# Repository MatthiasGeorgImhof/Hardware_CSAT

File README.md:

# Hardware_CSAT

Hardware design files for 1x cubesat:
- [EPS board](https://github.com/MatthiasGeorgImhof/Hardware_CSAT/tree/master/eps_board)
  - batteries and battery management for solar cells charging
  - voltage regulatars
  - RTC clock
- [Avionics board](https://github.com/MatthiasGeorgImhof/Hardware_CSAT/tree/master/avionics_board)
  - IMU and magnetometer
  - sun detectors
  - magnetorquer control
- [Science board](https://github.com/MatthiasGeorgImhof/Hardware_CSAT/tree/master/sci_board_wo_switches)
  - cameras and imagers
- [Communication board](https://github.com/MatthiasGeorgImhof/Hardware_CSAT/tree/master/comm_board)
  - 915 MHz link
  - ethernet port for satelite modem

In addition, there is also
- [Auxilliary board](https://github.com/MatthiasGeorgImhof/Hardware_CSAT/tree/master/aux_board) that stands provides desktop power and connectivity
  - USB connection to computer
  - voltage regulators

Schematics & Layouts are done using KiCad V9.0

The corresponding software repos are [AUXL496_CSAT for the auxilliary board](https://github.com/MatthiasGeorgImhof/AUXL496_CSAT) and [SCIL496_CSAT for the science board](https://github.com/MatthiasGeorgImhof/SCIL496_CSAT). Software is based on a common architecture [Common_CSAT](https://github.com/MatthiasGeorgImhof/Common_CSAT).

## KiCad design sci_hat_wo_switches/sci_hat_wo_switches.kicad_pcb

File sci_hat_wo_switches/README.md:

# Science Board

- STM32L496VGTx
- 2x CAN buses
- 3x camera ports
- 1x I2C port

 "Science board")

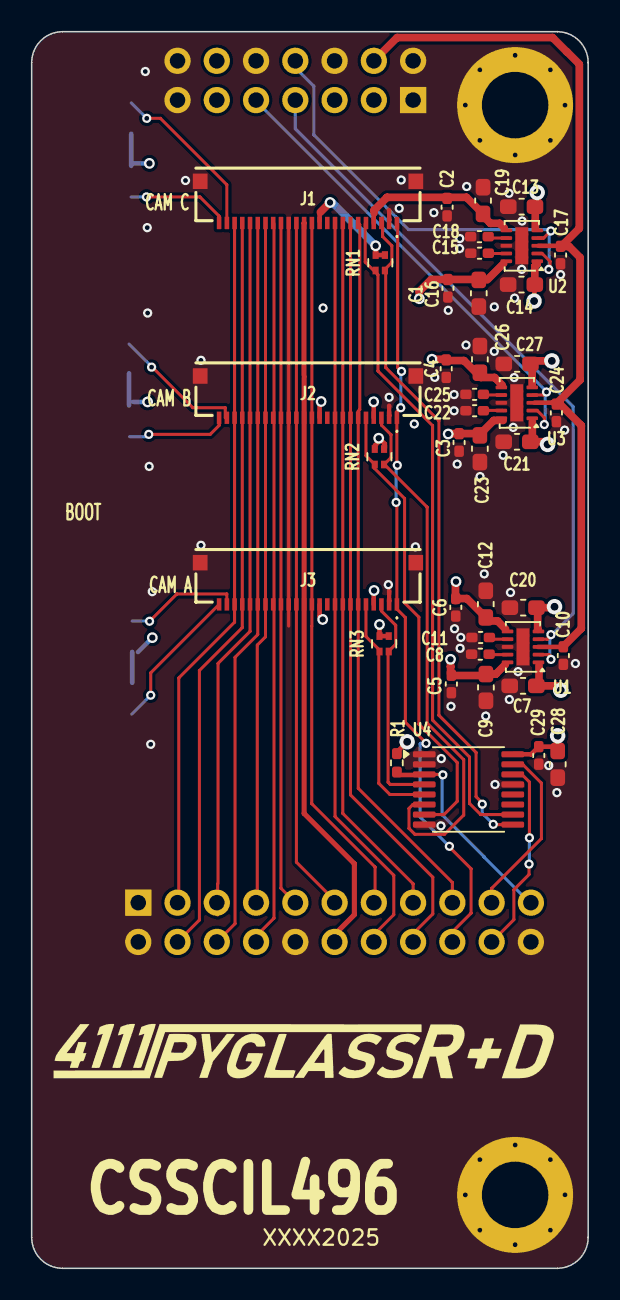
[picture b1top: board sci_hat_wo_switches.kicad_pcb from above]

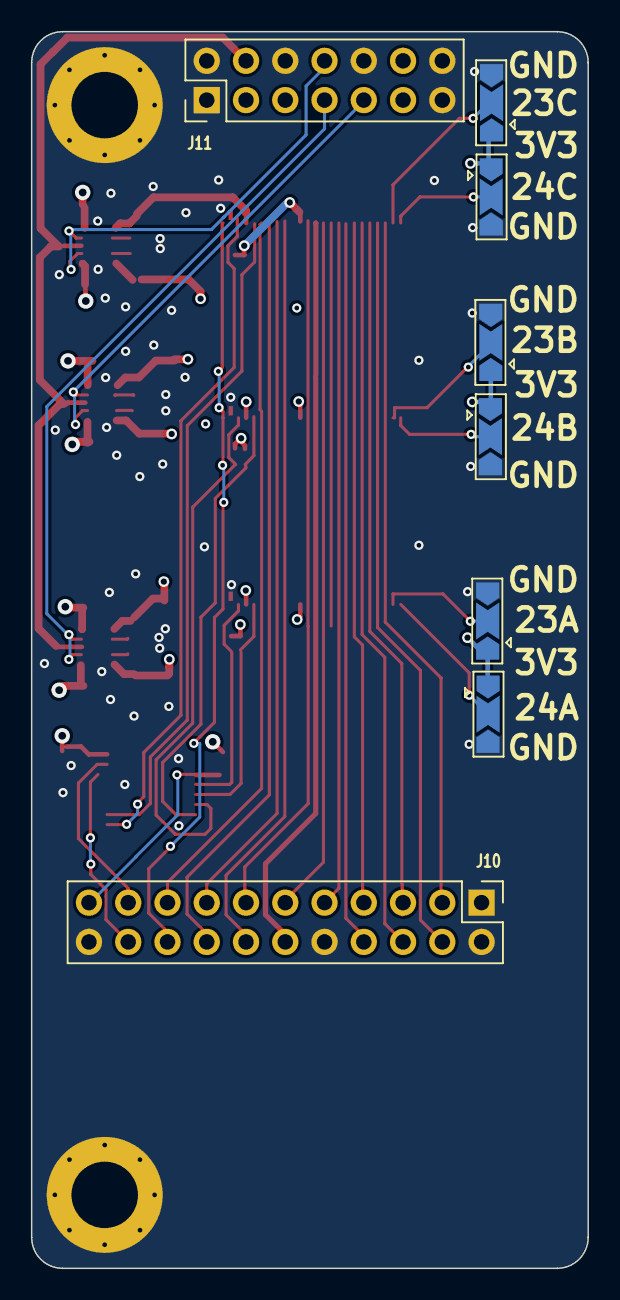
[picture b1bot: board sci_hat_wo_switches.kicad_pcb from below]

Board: 4 copper layers, 36.0 x 80.0 mm, 53 parts (8 on the bottom side), 52 nets.

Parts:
C1, C2, C3, C4, C5, C6, C10, C17, C24, C29: 100nF; C_0402_1005Metric_Pad0.74x0.62mm_HandSolder
C7, C13, C14, C20, C21, C27: 22uF; C_0603_1608Metric_Pad1.08x0.95mm_HandSolder
C8, C11, C15, C18, C22, C25: 220pF; C_0402_1005Metric_Pad0.74x0.62mm_HandSolder
C9, C12, C16, C19, C23, C26, C28: 10uF; C_0603_1608Metric_Pad1.08x0.95mm_HandSolder
H1, H2: MountingHole_Pad; MountingHole_4.3mm_M4_Pad_Via_Custom
J1, J2, J3: 10051922-2410EHLF; 100519222410EHLF
J10: Conn_02x11_Odd_Even; PinHeader_2x11_P2.54mm_Vertical
J11: Conn_02x07_Odd_Even; PinHeader_2x07_P2.54mm_Vertical
JP1, JP2, JP3, JP4, JP5, JP6: SolderJumper_3_Open; SolderJumper-3_P2.0mm_Open_TrianglePad1.0x1.5mm
NT1, NT2, NT3: NetTie_2; NetTie-2_SMD_Pad0.3mm
R1: 100K; R_0402_1005Metric_Pad0.72x0.64mm_HandSolder
RN1, RN2, RN3: 5K6; R_Array_Convex_2x0402_widepads
U1, U2, U3: TPS22968QDMGRQ1; WSON-10-1EP_2x3mm_P0.5mm_EP0.84x2.4mm
U4: TCA9546APWR; TSSOP-16_4.4x5mm_P0.65mm

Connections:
+1V8: C7.1, C14.1, C21.1, C28.1, C29.1, J11.5, R1.1, U1.1 (VIN1), U2.1 (VIN1), U3.1 (VIN1), U4.16 (VCC)
+2V8: C13.1, C20.1, C27.1, J11.3, U1.5 (VIN2), U2.5 (VIN2), U3.5 (VIN2)
+3.3V: C10.1, C17.1, C24.1, J11.4, U1.3 (VBIAS), U2.3 (VBIAS), U3.3 (VBIAS)
/CameraHat/1V8_A: C5.1, C9.1, J3.11, JP5.1 (A), JP6.1 (A), RN3.3 (R2.2), RN3.4 (R1.2), U1.10 (VOUT1)
/CameraHat/1V8_B: C3.1, C23.1, J2.11, JP3.1 (A), JP4.1 (A), RN2.3 (R2.2), RN2.4 (R1.2), U3.10 (VOUT1)
/CameraHat/1V8_C: C1.1, C16.1, J1.11, JP1.1 (A), JP2.1 (A), RN1.3 (R2.2), RN1.4 (R1.2), U2.10 (VOUT1)
/CameraHat/2V8_A: C6.1, C12.2, J3.4, U1.6 (VOUT2)
/CameraHat/2V8_B: C4.1, C26.2, J2.4, U3.6 (VOUT2)
/CameraHat/2V8_C: C2.1, C19.2, J1.4, U2.6 (VOUT2)
/CameraHat/Camera_A/A_GND: J3.2, NT3.1
/CameraHat/Camera_A/SCK: J3.5, RN3.1 (R1.1), U4.5 (SC0)
/CameraHat/Camera_A/SDA: J3.3, RN3.2 (R2.1), U4.4 (SD0)
/CameraHat/Camera_B/A_GND: J2.2, NT2.1
/CameraHat/Camera_B/SCK: J2.5, RN2.1 (R1.1), U4.7 (SC1)
/CameraHat/Camera_B/SDA: J2.3, RN2.2 (R2.1), U4.6 (SD1)
/CameraHat/Camera_C/A_GND: J1.2, NT1.1
/CameraHat/Camera_C/SCK: J1.5, RN1.1 (R1.1), U4.10 (SC2)
/CameraHat/Camera_C/SDA: J1.3, RN1.2 (R2.1), U4.9 (SD2)
/CameraHat/DCMI_00: J1.19, J2.19, J3.19, J10.6
/CameraHat/DCMI_01: J1.21, J2.21, J3.21, J10.4
/CameraHat/DCMI_02: J1.22, J2.22, J3.22, J10.3
/CameraHat/DCMI_03: J1.20, J2.20, J3.20, J10.5
/CameraHat/DCMI_04: J1.18, J2.18, J3.18, J10.7
/CameraHat/DCMI_05: J1.16, J2.16, J3.16, J10.9
/CameraHat/DCMI_06: J1.14, J2.14, J3.14, J10.11
/CameraHat/DCMI_07: J1.12, J2.12, J3.12, J10.13
/CameraHat/DCMI_HSYNC: J1.9, J2.9, J3.9, J10.14
/CameraHat/DCMI_PLXCLK: J1.17, J2.17, J3.17, J10.8
/CameraHat/DCMI_VSYNC: J1.7, J2.7, J3.7, J10.16
/CameraHat/ENABLE_A: J11.7, U1.2 (ON1), U1.4 (ON2)
/CameraHat/ENABLE_B: J11.9, U3.2 (ON1), U3.4 (ON2)
/CameraHat/ENABLE_C: J11.8, U2.2 (ON1), U2.4 (ON2)
/CameraHat/I2C_RST: J10.21, R1.2, U4.3 (RESET_N)
/CameraHat/I2C_SCK: J10.20, U4.14 (SCL)
/CameraHat/I2C_SDA: J10.19, U4.15 (SDA)
/CameraHat/PWRDN: J1.8, J2.8, J3.8, J10.15
/CameraHat/RESET: J1.6, J2.6, J3.6, J10.17
/CameraHat/STROBE: J1.1, J2.1, J3.1, J10.18
/CameraHat/XCLK: J1.13, J2.13, J3.13, J10.12
GND: C1.2, C2.2, C3.2, C4.2, C5.2, C6.2, C7.2, C8.2, C9.2, C10.2, C11.1, C12.1, C13.2, C14.2, C15.2, C16.2, C17.2, C18.1, C19.1, C20.2, C21.2, C22.2, C23.2, C24.2, C25.1, C26.1, C27.2, C28.2, C29.2, H1.1, H2.1, J1.15, J1.MP1, J1.MP2, J2.15, J2.MP1, J2.MP2, J3.15, J3.MP1, J3.MP2, J10.1, J10.2, J10.10, J10.22, J11.1, J11.2, J11.6, J11.10, J11.13, J11.14, JP1.3 (B), JP2.3 (B), JP3.3 (B), JP4.3 (B), JP5.3 (B), JP6.3 (B), NT1.2, NT2.2, NT3.2, U1.8 (GND), U1.11 (TPAD), U2.8 (GND), U2.11 (TPAD), U3.8 (GND), U3.11 (TPAD), U4.1 (A0), U4.2 (A1), U4.8 (GND), U4.13 (A2)
unnamed: J1.23, JP1.2 (C)
unnamed: J1.24, JP2.2 (C)
unnamed: J2.23, JP3.2 (C)
unnamed: J2.24, JP4.2 (C)
unnamed: J3.23, JP5.2 (C)
unnamed: J3.24, JP6.2 (C)
unnamed: C8.1, U1.9 (CT1)
unnamed: C11.2, U1.7 (CT2)
unnamed: C15.1, U2.9 (CT1)
unnamed: C18.2, U2.7 (CT2)
unnamed: C22.1, U3.9 (CT1)
unnamed: C25.2, U3.7 (CT2)

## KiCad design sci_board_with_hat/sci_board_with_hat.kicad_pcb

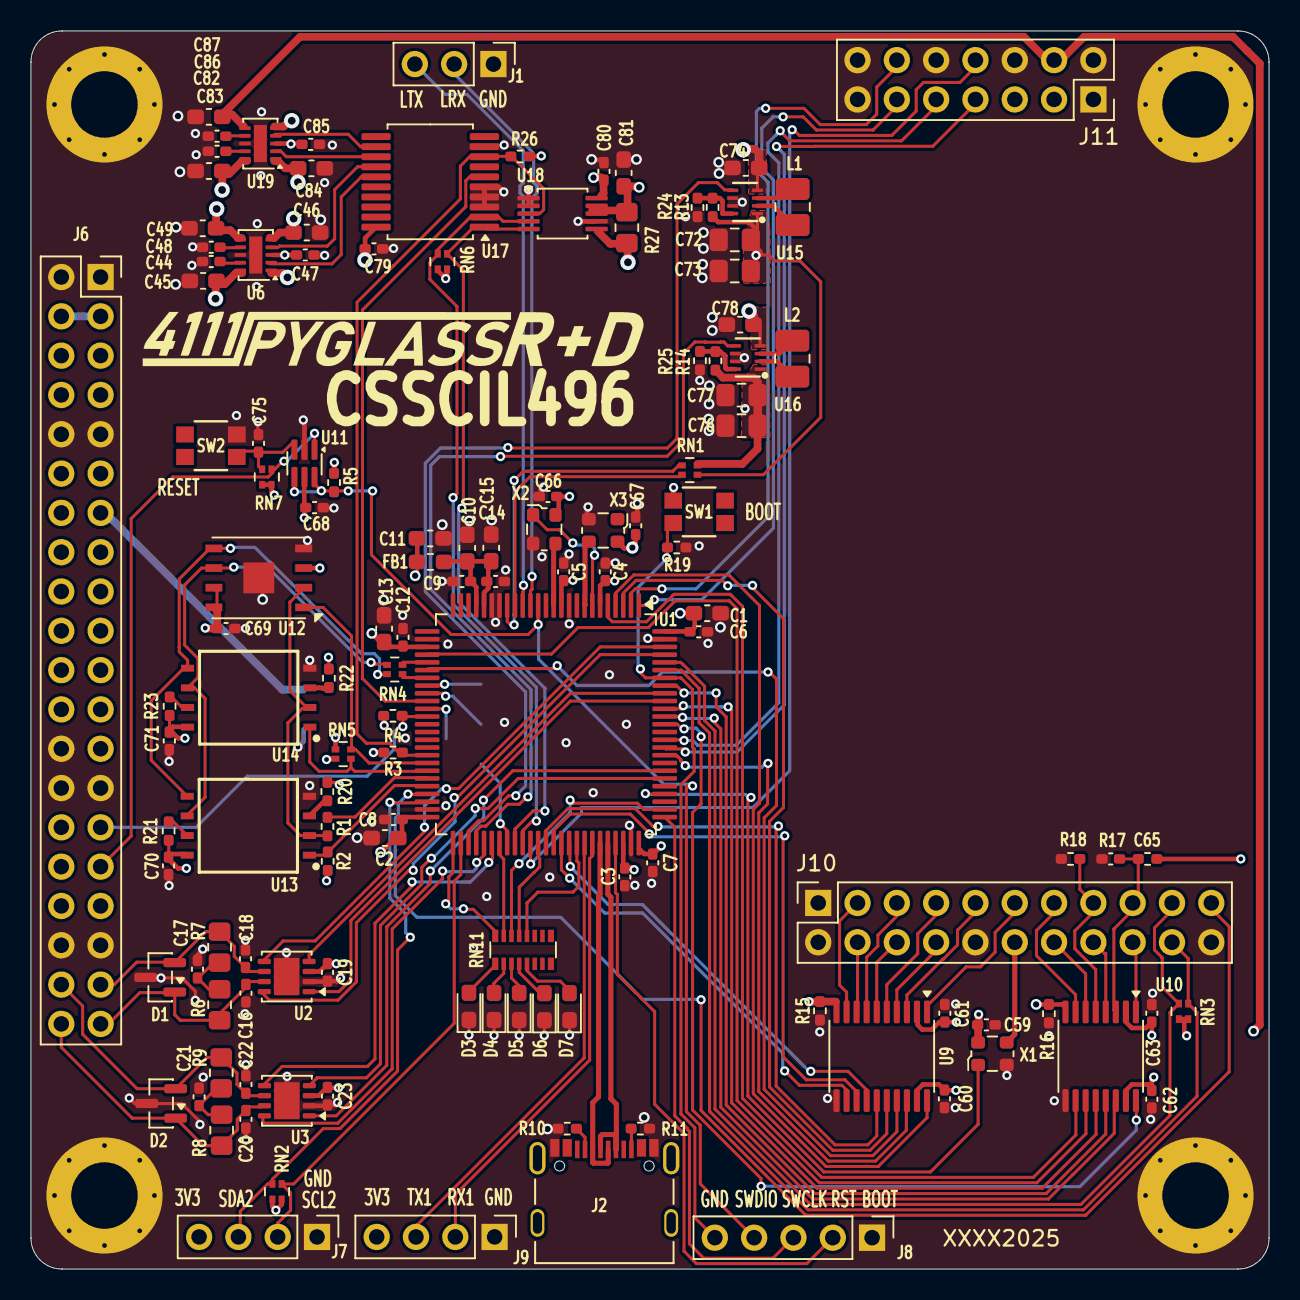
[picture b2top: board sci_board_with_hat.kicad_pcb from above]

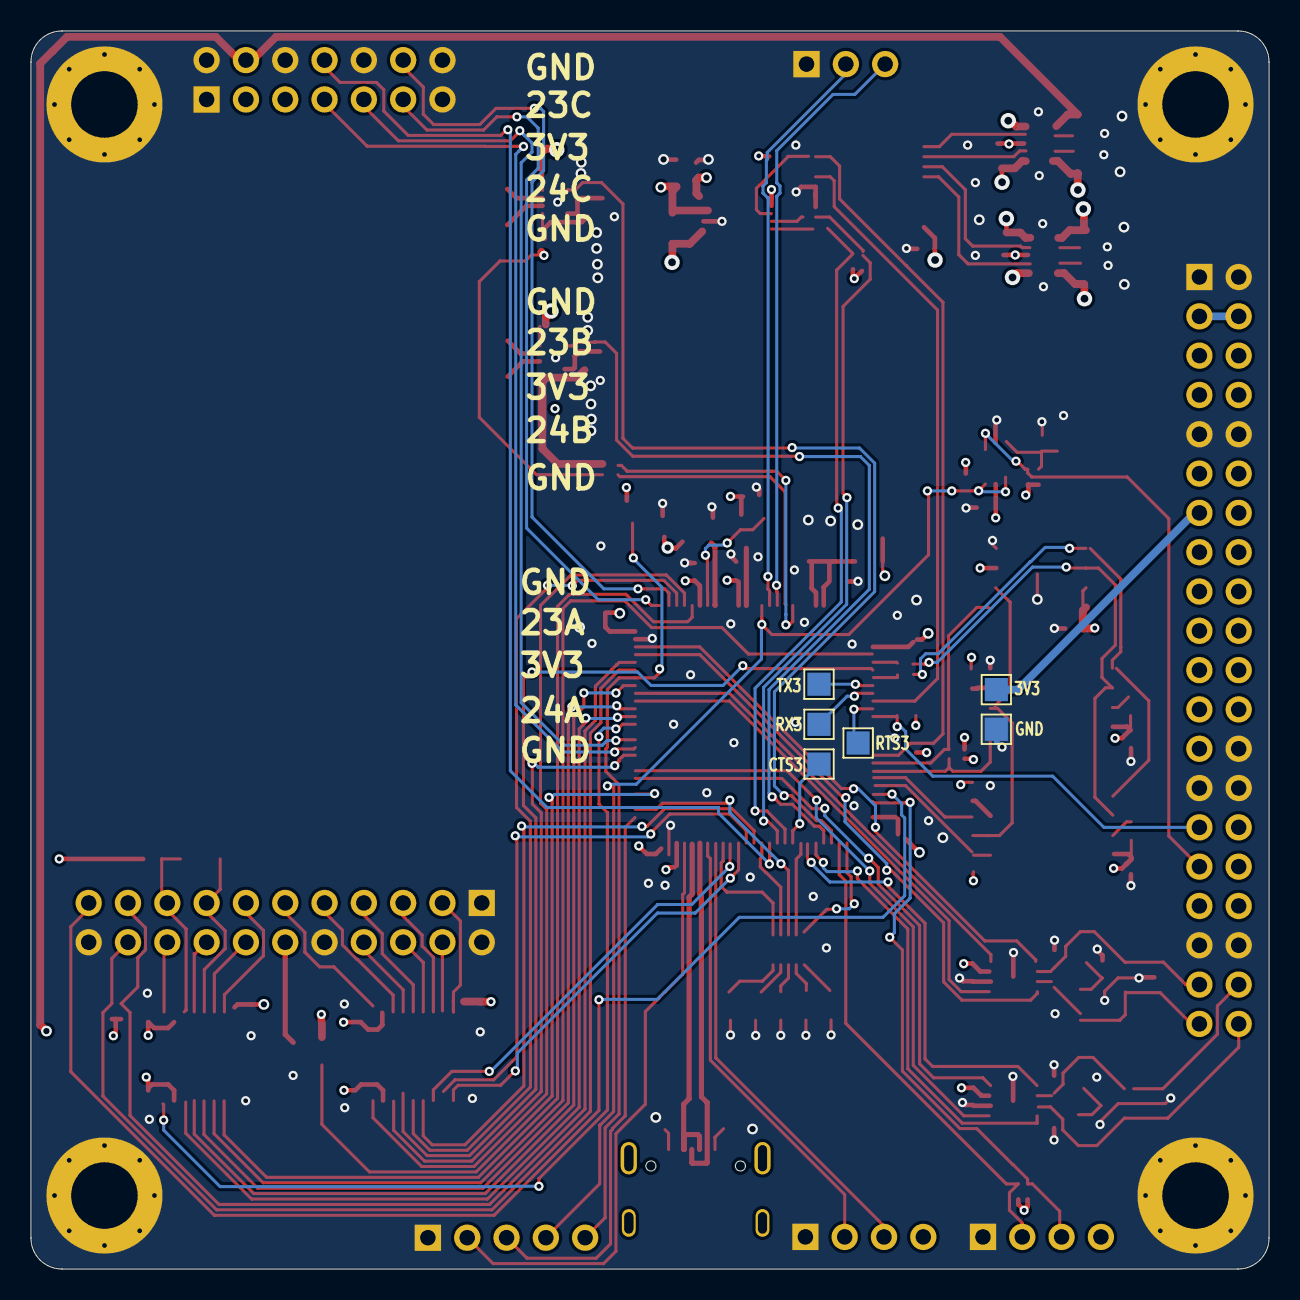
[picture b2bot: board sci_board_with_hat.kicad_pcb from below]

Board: 4 copper layers, 80.0 x 80.0 mm, 139 parts (6 on the bottom side), 134 nets.

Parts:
C1, C2, C10, C11, C13, C15, C81: 10uF; C_0603_1608Metric_Pad1.08x0.95mm_HandSolder
C3, C4, C5, C6, C7, C8, C9, C12, C14, C59, C60, C61, C62, C63, C65, C79, C80: 100nF; C_0402_1005Metric_Pad0.74x0.62mm_HandSolder
C16, C18, C20, C22: 100p; C_0402_1005Metric_Pad0.74x0.62mm_HandSolder
C17, C21: 4n7; C_0402_1005Metric_Pad0.74x0.62mm_HandSolder
C19, C23, C47, C66, C67, C68, C69, C70, C71, C75, C85: 100n; C_0402_1005Metric_Pad0.74x0.62mm_HandSolder
C44, C48, C82, C86: 220pF; C_0402_1005Metric_Pad0.74x0.62mm_HandSolder
C45, C49, C83, C87: 10u; C_0603_1608Metric_Pad1.08x0.95mm_HandSolder
C46, C84: 22u; C_0603_1608Metric_Pad1.08x0.95mm_HandSolder
C72, C73, C76, C77: 47uF; C_0805_2012Metric_Pad1.18x1.45mm_HandSolder
C74, C78: 22uF; C_0603_1608Metric_Pad1.08x0.95mm_HandSolder
D1, D2: NUP2105LT1G; SOT-23
D3: RED; LED_0603_1608Metric_Pad1.05x0.95mm_HandSolder
D4: GREEN; LED_0603_1608Metric_Pad1.05x0.95mm_HandSolder
D5, D6, D7: YELLOW; LED_0603_1608Metric_Pad1.05x0.95mm_HandSolder
FB1: 120R; L_0603_1608Metric_Pad1.05x0.95mm_HandSolder
H1, H2, H3, H4: MountingHole_Pad; MountingHole_4.3mm_M4_Pad_Via_Custom
J1: Conn_01x03_Pin Vertical; PinHeader_1x03_P2.54mm_Vertical
J2: 10155435-00011LF; AMPHENOL_10155435-00011LF
J6: PC104 Conn_02x20_Odd_Even; PinSocket_2x20_P2.54mm_Vertical
J7, J9: Conn_01x04_Pin Vertical; PinHeader_1x04_P2.54mm_Vertical
J8: Conn_01x05_Pin Vertical; PinHeader_1x05_P2.54mm_Vertical
J10: Conn_02x11_Odd_Even; PinSocket_2x11_P2.54mm_Vertical
J11: Conn_02x07_Odd_Even; PinSocket_2x07_P2.54mm_Vertical
L1, L2: 1uH; L_1008_2520Metric_Pad1.43x2.20mm_HandSolder
R1: 22R; R_0402_1005Metric_Pad0.72x0.64mm_HandSolder
R2, R3, R5, R15, R16, R17, R18, R19, R20, R21, R22, R23, R26: 100K; R_0402_1005Metric_Pad0.72x0.64mm_HandSolder
R4: 330K; R_0402_1005Metric_Pad0.72x0.64mm_HandSolder
R6, R7, R8, R9: 60R4; R_0805_2012Metric_Pad1.20x1.40mm_HandSolder
R10, R11: 5K1; R_0402_1005Metric_Pad0.72x0.64mm_HandSolder
R13: 422K; R_0402_1005Metric_Pad0.72x0.64mm_HandSolder
R14: 237K; R_0402_1005Metric_Pad0.72x0.64mm_HandSolder
R24, R25: 91K; R_0402_1005Metric_Pad0.72x0.64mm_HandSolder
R27: 10m; R_0805_2012Metric_Pad1.20x1.40mm_HandSolder
RN1: 10K; R_Array_Convex_2x0402_widepads
RN2, RN3, RN6: 5K6; R_Array_Convex_2x0402_widepads
RN4: 22R; R_Array_Convex_2x0402_widepads
RN5, RN7: 100K; R_Array_Convex_2x0402_widepads
RN11: 1K; R_Array_Convex_8x0602_widepads
SW1, SW2: EVP-AA602W; EVP602AA
TP1: TX3; TestPoint_Pad_1.5x1.5mm
TP2: RX3; TestPoint_Pad_1.5x1.5mm
TP3: RTS3; TestPoint_Pad_1.5x1.5mm
TP4: CTS3; TestPoint_Pad_1.5x1.5mm
TP5: 3V3AUX; TestPoint_Pad_1.5x1.5mm
TP6: GND; TestPoint_Pad_1.5x1.5mm
U1: STM32L496VGTx; LQFP-100_14x14mm_P0.5mm
U2, U3: TCAN3414; VSON-8-1EP_3x3mm_P0.65mm_EP1.65x2.4mm
U6, U19: TPS22968QDMGRQ1; WSON-10-1EP_2x3mm_P0.5mm_EP0.84x2.4mm
U9: TXB0108PWR; TSSOP-20_4.4x6.5mm_P0.65mm
U10: TXB0106PWR; TSSOP-16_4.4x5mm_P0.65mm
U11: 74LVC2G07; SOT-363_SC-70-6
U12: MR25H10; DFN-8-1EP_6x5mm_P1.27mm_EP2x2mm
U13, U14: MT29F4G01ABAFDWB-IT:F TR; SON127P800X600X65-8N
U15, U16: TPS631000DRLR; TPS631000DRLR_TEX
U17: MCP23008T-E/SS; SSOP-20_5.3x7.2mm_P0.65mm
U18: INA226AIDGSR; VSSOP-10_3x3mm_P0.5mm
X1: 24MHz; Oscillator_SMD_ECS_2520MV-xxx-xx-4Pin_2.5x2.0mm
X2: 10MHz; Oscillator_SMD_ECS_2520MV-xxx-xx-4Pin_2.5x2.0mm
X3: 32.768KHZ; Oscillator_SMD_ECS_2520MV-xxx-xx-4Pin_2.5x2.0mm

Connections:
+3V3_AUX: C79.1, C80.1, J6.13, R26.1, R27.1, RN6.3 (R2.2), RN6.4 (R1.2), TP5.1, U17.20 (VDD), U18.6 (VS), U18.10 (IN+)
+3V3_STM32_Core: C1.2, C2.2, C3.1, C4.1, C5.1, C6.1, C7.1, C8.1, C11.1, C12.2, C13.2, C19.1, C23.1, C66.1, C67.1, C68.2, FB1.1, J6.14, J9.4, R3.1, R4.1, R5.1, RN7.1 (R1.1), RN7.2 (R2.1), SW1.1, U1.6 (VBAT), U1.11 (VDD), U1.28 (VDD), U1.50 (VDD), U1.73 (VDDUSB), U1.75 (VDD), U1.100 (VDD), U2.3 (VCC), U3.3 (VCC), U11.5 (VCC), X2.4 (VDD), X3.4 (VCC)
+BATT: C74.1, C78.1, J6.8, U15.4 (VIN), U16.4 (VIN)
/1V8: C59.1, C61.1, C63.1, C76.1, C77.1, J11.5, R14.1, R15.1, R16.1, R17.1, RN1.2 (R2.1), U9.2 (VCCA), U9.10 (OE), U10.2 (VCCA), U10.8 (OE), U16.1 (VOUT), X1.4 (VDD)
/2V8: C72.1, C73.1, J11.3, R13.1, RN1.1 (R1.1), U15.1 (VOUT)
/3V3_Cameras: C60.1, C62.1, C87.2, J11.4, RN3.3 (R2.2), RN3.4 (R1.2), U9.19 (VCCB), U10.15 (VCCB), U19.6 (VOUT2)
/3V3_Flash: C49.2, C70.1, C71.1, R2.1, R20.1, R21.1, R22.1, R23.1, RN5.2 (R2.1), U6.6 (VOUT2), U13.8 (VCC), U14.8 (VCC)
/3V3_Imager: C83.1, J7.4, RN2.3 (R2.2), RN2.4 (R1.2), U19.10 (VOUT1)
/3V3_MRAM: C45.1, C69.1, RN5.1 (R1.1), U6.10 (VOUT1), U12.3 (~WP), U12.7 (~HOLD), U12.8 (VDD)
/ATTN: J6.29, R4.2, U1.37 (PB2)
/Aux Power Switch 3V3/ENABLE0: U17.12 (GP0), U19.4 (ON2)
/Aux Power Switch 3V3/ENABLE1: U17.13 (GP1), U19.2 (ON1)
/Aux Power Switch 3V3/ENABLE2: U6.4 (ON2), U17.14 (GP2)
/Aux Power Switch 3V3/ENABLE3: U6.2 (ON1), U17.15 (GP3)
/Aux Power Switch 3V3/RESET: U1.35 (PB0), U17.6 (*RESET)
/Aux Power Switch 3V3/VBUS: C46.1, C47.1, C81.1, C84.1, C85.1, R27.2, U6.1 (VIN1), U6.3 (VBIAS), U6.5 (VIN2), U18.8 (VBUS), U18.9 (IN-), U19.1 (VIN1), U19.3 (VBIAS), U19.5 (VIN2)
/CAN1_H: C20.1, D2.1 (K), J6.40, R8.1, U3.7 (CANH)
/CAN1_L: C22.2, D2.2 (K), J6.38, R9.2, U3.6 (CANL)
/CAN1_RX: U1.81 (PD0), U3.4 (RXD)
/CAN1_SHDN: U1.56 (PD9), U3.5 (SHTD)
/CAN1_STB: U1.55 (PD8), U3.8 (STB)
/CAN1_TX: U1.82 (PD1), U3.1 (TXD)
/CAN2_H: C16.1, D1.1 (K), J6.39, R6.1, U2.7 (CANH)
/CAN2_L: C18.2, D1.2 (K), J6.37, R7.2, U2.6 (CANL)
/CAN2_RX: U1.92 (PB6), U2.4 (RXD)
/CAN2_SHDN: U1.98 (PE1), U2.5 (SHTD)
/CAN2_STB: U1.97 (PE0), U2.8 (STB)
/CAN2_TX: U1.91 (PB5), U2.1 (TXD)
/Cameras/*RESET_1V8: C65.1, J10.17, R17.2, U10.3 (A2)
/Cameras/CLK_OE: U1.79 (PC11), X1.1 (TRI-STATE)
/Cameras/DCMI_00: U1.63 (PC6), U9.15 (B5)
/Cameras/DCMI_01: U1.64 (PC7), U9.13 (B7)
/Cameras/DCMI_02: U1.65 (PC8), U9.12 (B8)
/Cameras/DCMI_03: U1.66 (PC9), U9.14 (B6)
/Cameras/DCMI_04: U1.3 (PE4), U9.16 (B4)
/Cameras/DCMI_05: U1.84 (PD3), U9.18 (B2)
/Cameras/DCMI_06: U1.4 (PE5), U9.20 (B1)
/Cameras/DCMI_07: U1.5 (PE6), U10.10 (B6)
/Cameras/DCMI_D0_1V8: J10.6, U9.6 (A5)
/Cameras/DCMI_D1_1V8: J10.4, U9.8 (A7)
/Cameras/DCMI_D2_1V8: J10.3, U9.9 (A8)
/Cameras/DCMI_D3_1V8: J10.5, U9.7 (A6)
/Cameras/DCMI_D4_1V8: J10.7, U9.5 (A4)
/Cameras/DCMI_D5_1V8: J10.9, U9.3 (A2)
/Cameras/DCMI_D6_1V8: J10.11, U9.1 (A1)
/Cameras/DCMI_D7_1V8: J10.13, U10.7 (A6)
/Cameras/DCMI_HSYNC: U1.29 (PA4), U10.11 (B5)
/Cameras/DCMI_HSYNC_1V8: J10.14, U10.6 (A5)
/Cameras/DCMI_PLXCLK: U1.31 (PA6), U9.17 (B3)
/Cameras/DCMI_PLXCLK_1V8: J10.8, U9.4 (A3)
/Cameras/DCMI_VSYNC: U1.93 (PB7), U10.13 (B3)
/Cameras/DCMI_VSYNC_1V8: J10.16, U10.4 (A3)
/Cameras/ENABLE_1V8: U1.54 (PB15), U16.5 (EN)
/Cameras/ENABLE_2V8: U1.53 (PB14), U15.5 (EN)
/Cameras/ENABLE_A: J11.7, U1.85 (PD4)
/Cameras/ENABLE_B: J11.9, U1.86 (PD5)
/Cameras/ENABLE_C: J11.8, U1.61 (PD14)
/Cameras/I2C_RST: J10.21, U1.47 (PB10)
/Cameras/PWRDN: U1.90 (PB4), U10.12 (B4)
/Cameras/PWRDN_1V8: J10.15, R18.1, U10.5 (A4)
/Cameras/Power Regulator 1V8/LX1: L2.2, U16.3 (LX1)
/Cameras/Power Regulator 1V8/LX2: L2.1, U16.2 (LX2)
/Cameras/Power Regulator 1V8/R-: R14.2, R25.1, U16.8 (FB)
/Cameras/Power Regulator 2V8/LX1: L1.2, U15.3 (LX1)
/Cameras/Power Regulator 2V8/LX2: L1.1, U15.2 (LX2)
/Cameras/Power Regulator 2V8/R-: R13.2, R24.1, U15.8 (FB)
/Cameras/RESET: U1.89 (PB3), U10.14 (B2)
/Cameras/S0: J11.11, U1.1 (PE2)
/Cameras/S1: J11.12, U1.2 (PE3)
/Cameras/STROBE: U1.88 (PD7), U10.16 (B1)
/Cameras/STROBE_1V8: J10.18, U10.1 (A1)
/Cameras/XCLK: J10.12, X1.3 (OUTPUT)
/Flash1/SPI_CLK: RN4.1 (R1.1), U12.6 (SCK), U13.6 (SCK), U14.6 (SCK)
/Flash1/SPI_MISO: R1.2, U12.2 (SO), U13.2 (SO/IO1), U14.2 (SO/IO1)
/Flash1/SPI_MOSI: RN4.2 (R2.1), U12.5 (SI), U13.5 (SI/IO0), U14.5 (SI/IO0)
/I2C1_SCK: J10.20, RN3.1 (R1.1), U1.95 (PB8)
/I2C1_SDA: J10.19, RN3.2 (R2.1), U1.96 (PB9)
/I2C2_SCK: J7.2, RN2.1 (R1.1), U1.52 (PB13)
/I2C2_SDA: J7.3, RN2.2 (R2.1), U1.48 (PB11)
/I2C4_SCK: RN6.1 (R1.1), U1.59 (PD12), U17.1 (SCL), U18.5 (SCL)
/I2C4_SDA: RN6.2 (R2.1), U1.60 (PD13), U17.2 (SDA), U18.4 (SDA)
/INTERBOARD CONNECTOR/BATT: J6.3, J6.4
/PMIC/ADC3_IN3: RN1.4 (R1.2), U1.17 (PC2)
/PMIC/ADC3_IN4: RN1.3 (R2.2), U1.18 (PC3)
/PMIC/BOOT0: J8.5, R19.1, SW1.2, U1.94 (PH3)
/PMIC/LED1: RN11.16 (R), U1.51 (PB12)
/PMIC/LED2: RN11.15 (R), U1.57 (PD10)
/PMIC/LED3: RN11.14 (R), U1.77 (PA15)
/PMIC/LED4: RN11.13 (R), U1.62 (PD15)
/PMIC/LED5: RN11.12 (R), U1.67 (PA8)
/PMIC/LPUART_RX: J1.2, U1.15 (PC0)
/PMIC/LPUART_TX: J1.3, U1.16 (PC1)
/PMIC/NRST: J8.4, R5.2, U1.14 (NRST), U11.4 (OUT2), U11.6 (OUT1)
/PMIC/OSC32_IN: U1.8 (PC14), X3.3 (OUT)
/PMIC/OSC_HSE_IN: U1.12 (PH0), X2.3 (OUTPUT)
/PMIC/OSC_HSE_OE: U1.7 (PC13), X2.1 (TRI-STATE)
/PMIC/RESET: C75.1, RN7.4 (R1.2), SW2.3, U11.3 (IN2)
/PMIC/SPI1_MISO: R1.1, U1.45 (PE14)
/PMIC/SPI1_MOSI: RN4.3 (R2.2), U1.32 (PA7)
/PMIC/SPI1_SCK: RN4.4 (R1.2), U1.30 (PA5)
/PMIC/SWCLK: J8.3, U1.76 (PA14)
/PMIC/SWDIO: J8.2, U1.72 (PA13)
/PMIC/USART1_RX: J9.2, U1.69 (PA10)
/PMIC/USART1_TX: J9.3, U1.68 (PA9)
/PMIC/USART3_CTS: TP4.1, U1.58 (PD11)
/PMIC/USART3_RTS: TP3.1, U1.36 (PB1)
/PMIC/USART3_RX: TP2.1, U1.34 (PC5)
/PMIC/USART3_TX: TP1.1, U1.33 (PC4)
/PMIC/USB_OTG_FS_DM: J2.A7 (DN1_A), J2.B7 (DN2_B), U1.70 (PA11)
/PMIC/USB_OTG_FS_DP: J2.A6 (DP1_A), J2.B6 (DP2_B), U1.71 (PA12)
/PMIC/VDDA: C9.1, C10.1, C14.2, C15.2, FB1.2, U1.21 (VREF+), U1.22 (VDDA)
/Power_INT: R3.2, R26.2, U1.42 (PE11), U17.8 (INT), U18.3 (ALERT)
/SCI_RESET: J6.31, RN7.3 (R2.2), U11.1 (IN1)
/SPI1_CS_FLASH1: R2.2, U1.46 (PE15), U13.1 (CS#)
/SPI1_CS_FLASH2: RN5.3 (R2.2), U1.44 (PE13), U14.1 (CS#)
/SPI1_CS_MRAM: RN5.4 (R1.2), U1.43 (PE12), U12.1 (~CS)
GND: C1.1, C2.1, C3.2, C4.2, C5.2, C6.2, C7.2, C8.2, C9.2, C10.2, C11.2, C12.1, C13.1, C14.1, C15.1, C16.2, C17.2, C18.1, C19.2, C20.2, C21.2, C22.1, C23.2, C44.2, C45.2, C46.2, C47.2, C48.1, C49.1, C59.2, C60.2, C61.2, C62.2, C63.2, C65.2, C66.2, C67.2, C68.1, C69.2, C70.2, C71.2, C72.2, C73.2, C74.2, C75.2, C76.2, C77.2, C78.2, C79.2, C80.2, C81.2, C82.2, C83.2, C84.2, C85.2, C86.1, C87.1, D1.3 (A), D2.3 (A), D3.1 (K), D4.1 (K), D5.1 (K), D6.1 (K), D7.1 (K), H1.1, H2.1, H3.1, H4.1, J1.1, J2.A1_B12 (GND), J2.B1_A12 (GND__1), J6.1, J6.2, J6.9, J6.10, J6.26, J6.27, J6.28, J6.35, J6.36, J7.1, J8.1, J9.1, J10.1, J10.2, J10.10, J10.22, J11.1, J11.2, J11.6, J11.10, J11.13, J11.14, R10.1, R11.1, R15.2, R16.2, R18.2, R19.2, R24.2, R25.2, SW2.4, TP6.1, U1.10 (VSS), U1.19 (VSSA), U1.20 (VREF-), U1.27 (VSS), U1.49 (VSS), U1.74 (VSS), U1.99 (VSS), U2.2 (GND), U2.9 (GND), U3.2 (GND), U3.9 (GND), U6.8 (GND), U6.11 (TPAD), U9.11 (GND), U10.9 (GND), U11.2 (GND), U12.4 (VSS), U12.9 (PAD), U13.4 (VSS), U14.4 (VSS), U15.6 (MODE), U15.7 (GND), U16.6 (MODE), U16.7 (GND), U17.3 (A2), U17.4 (A1), U17.5 (A0), U17.9 (VSS), U18.1 (A1), U18.2 (A0), U18.7 (GND), U19.8 (GND), U19.11 (TPAD), X1.2 (GND), X2.2 (GND), X3.2 (GND)
unnamed: C17.1, R6.2, R7.1
unnamed: C21.1, R8.2, R9.1
unnamed: D3.2 (A), RN11.1 (R)
unnamed: D4.2 (A), RN11.2 (R)
unnamed: D5.2 (A), RN11.3 (R)
unnamed: D6.2 (A), RN11.4 (R)
unnamed: D7.2 (A), RN11.5 (R)
unnamed: J2.A5 (CC1_A), R10.2
unnamed: J2.B5 (CC2_B), R11.2
unnamed: C44.1, U6.9 (CT1)
unnamed: C48.2, U6.7 (CT2)
unnamed: R21.2, U13.7 (HOLD#/IO3)
unnamed: R20.2, U13.3 (WP#/IO2)
unnamed: R23.2, U14.7 (HOLD#/IO3)
unnamed: R22.2, U14.3 (WP#/IO2)
unnamed: C82.1, U19.9 (CT1)
unnamed: C86.2, U19.7 (CT2)

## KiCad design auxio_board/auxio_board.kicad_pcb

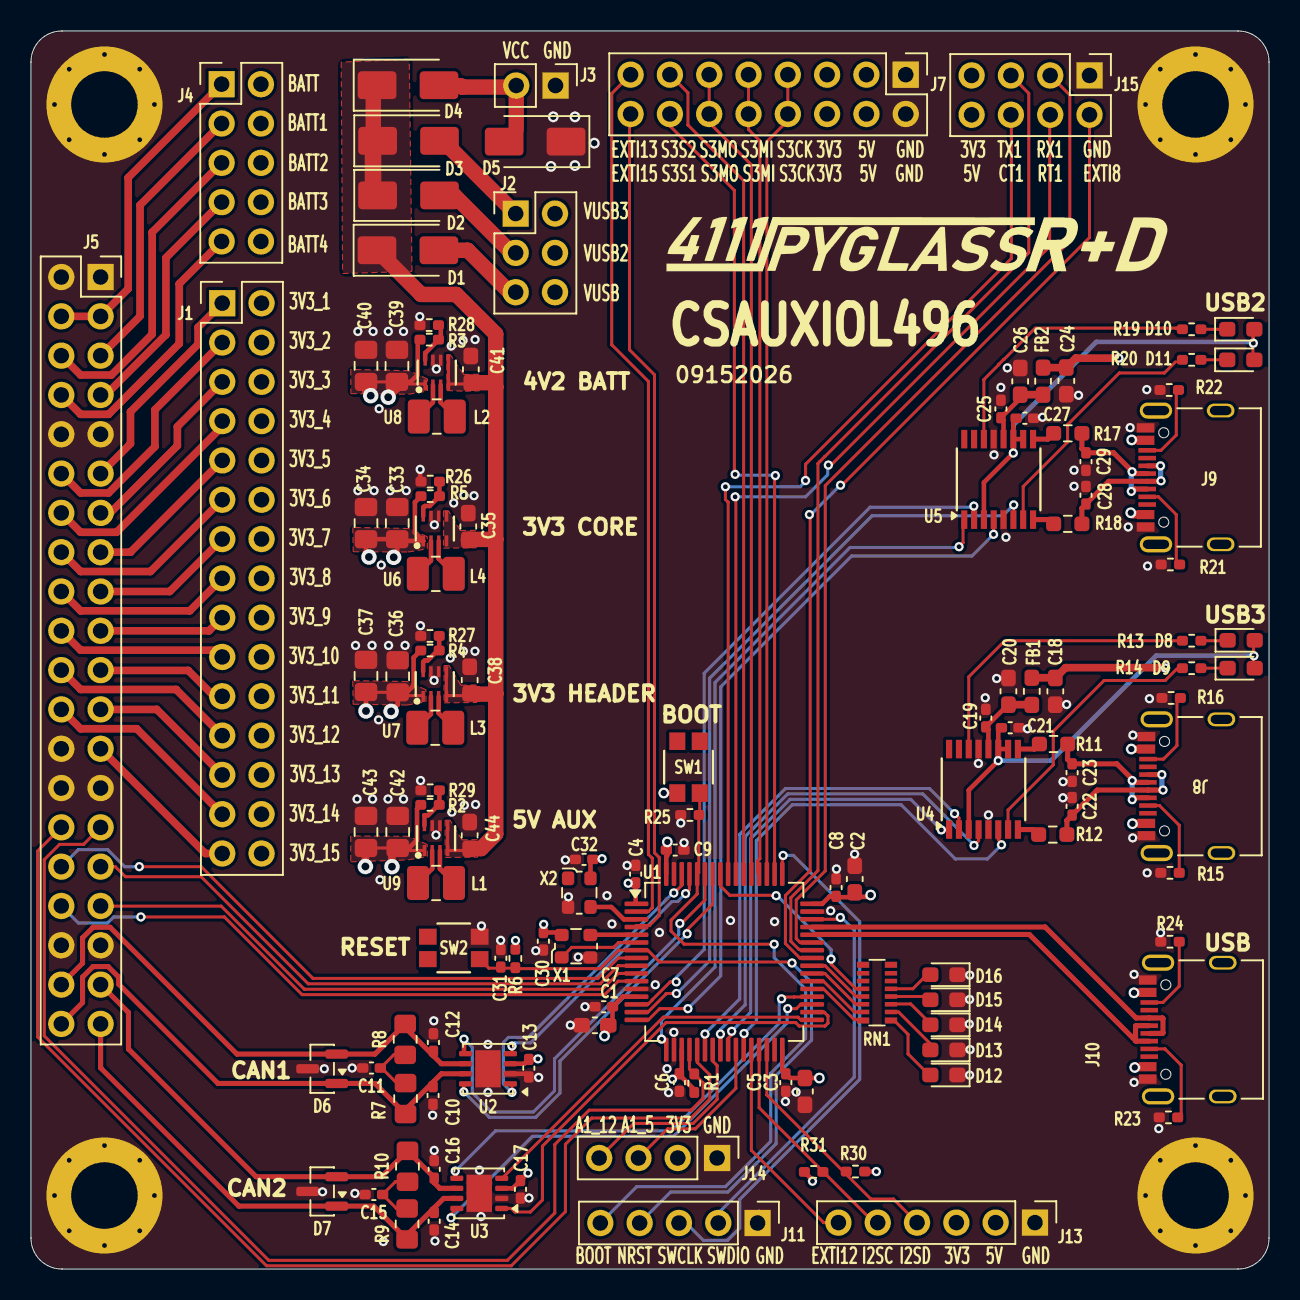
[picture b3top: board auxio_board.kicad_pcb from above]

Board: 4 copper layers, 80.0 x 80.0 mm, 128 parts (0 on the bottom side), 135 nets.

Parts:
C1, C2, C3, C18, C20, C24, C26: 10uF; C_0603_1608Metric_Pad1.08x0.95mm_HandSolder
C4, C5, C6, C7, C8, C9, C19, C21, C25, C27: 100nF; C_0402_1005Metric_Pad0.74x0.62mm_HandSolder
C10, C12, C14, C16: 100p; C_0402_1005Metric_Pad0.74x0.62mm_HandSolder
C11, C15: 4n7; C_0402_1005Metric_Pad0.74x0.62mm_HandSolder
C13, C17, C30, C31, C32: 100n; C_0402_1005Metric_Pad0.74x0.62mm_HandSolder
C22, C23, C28, C29: 47pF; C_0402_1005Metric_Pad0.74x0.62mm_HandSolder
C33, C34, C36, C37, C39, C40, C42, C43: 47uF; C_0805_2012Metric_Pad1.18x1.45mm_HandSolder
C35, C38, C41, C44: 22uF; C_0603_1608Metric_Pad1.08x0.95mm_HandSolder
D1, D2, D3, D4: CDBA240LL-HF; D_SMA
D5: SMAJ6.0CA; D_SMA
D6, D7: NUP2105LT1G; SOT-23
D8, D10: LED_SMD_GREEN; LED_0603_1608Metric_Pad1.05x0.95mm_HandSolder
D9, D11: LED_SMD_RED; LED_0603_1608Metric_Pad1.05x0.95mm_HandSolder
D12: RED; LED_0603_1608Metric_Pad1.05x0.95mm_HandSolder
D13: GREEN; LED_0603_1608Metric_Pad1.05x0.95mm_HandSolder
D14, D15, D16: YELLOW; LED_0603_1608Metric_Pad1.05x0.95mm_HandSolder
FB1, FB2: 120R; L_0603_1608Metric_Pad1.05x0.95mm_HandSolder
H1, H2, H3, H4: MountingHole_Pad; MountingHole_4.3mm_M4_Pad_Via_Custom
J1: Conn_02x15_Odd_Even; PinHeader_2x15_P2.54mm_Vertical
J2: Conn_02x03_Odd_Even; PinHeader_2x03_P2.54mm_Vertical
J3: Conn_01x02_Pin; PinHeader_1x02_P2.54mm_Vertical
J4: Conn_02x05_Odd_Even; PinHeader_2x05_P2.54mm_Vertical
J5: PC104 Conn_02x20_Odd_Even; PinSocket_2x20_P2.54mm_Vertical
J7: Conn_02x08_Odd_Even; PinHeader_2x08_P2.54mm_Vertical
J8, J9, J10: 10155435-00011LF; AMPHENOL_10155435-00011LF
J11: Conn_01x05_Pin Vertical; PinHeader_1x05_P2.54mm_Vertical
J13: Conn_01x06_Pin; PinHeader_1x06_P2.54mm_Vertical
J14: Conn_01x04_Pin; PinHeader_1x04_P2.54mm_Vertical
J15: Conn_02x04_Odd_Even; PinHeader_2x04_P2.54mm_Vertical
L1, L2, L3, L4: 1uH; L_1008_2520Metric_Pad1.43x2.20mm_HandSolder
R1: 330K; R_0402_1005Metric_Pad0.72x0.64mm_HandSolder
R2: 806K; R_0402_1005Metric_Pad0.72x0.64mm_HandSolder
R3: 665K; R_0402_1005Metric_Pad0.72x0.64mm_HandSolder
R4, R5: 511K; R_0402_1005Metric_Pad0.72x0.64mm_HandSolder
R6, R25: 100K; R_0402_1005Metric_Pad0.72x0.64mm_HandSolder
R7, R8, R9, R10: 60R4; R_0805_2012Metric_Pad1.20x1.40mm_HandSolder
R11, R12, R17, R18: 27R; R_0603_1608Metric_Pad0.98x0.95mm_HandSolder
R13, R14, R19, R20: 1K; R_0402_1005Metric_Pad0.72x0.64mm_HandSolder
R15, R16, R21, R22, R23, R24, R30, R31: 5K1; R_0402_1005Metric_Pad0.72x0.64mm_HandSolder
R26, R27, R28, R29: 91K; R_0402_1005Metric_Pad0.72x0.64mm_HandSolder
RN1: 1K; R_Array_Convex_8x0602_widepads
SW1, SW2: EVP-AA602W; EVP602AA
U1: STM32L496RGT6; LQFP-64_10x10mm_P0.5mm
U2, U3: TCAN3414; VSON-8-1EP_3x3mm_P0.65mm_EP1.65x2.4mm
U4, U5: FT230XS; SSOP-16_3.9x4.9mm_P0.635mm
U6, U7, U8, U9: TPS631000DRLR; TPS631000DRLR_TEX
X1: 10MHz; Oscillator_SMD_ECS_2520MV-xxx-xx-4Pin_2.5x2.0mm
X2: 32.768KHZ; Oscillator_SMD_ECS_2520MV-xxx-xx-4Pin_2.5x2.0mm

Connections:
+3V3: C36.1, C37.1, J1.2, J1.4, J1.6, J1.8, J1.10, J1.12, J1.14, J1.16, J1.18, J1.20, J1.22, J1.24, J1.26, J1.28, J1.30, R4.2, U7.1 (VOUT)
+3V3_Core: C1.1, C2.1, C3.1, C4.1, C5.1, C6.1, C7.1, C8.1, C9.1, C13.1, C17.1, C30.1, C32.1, C33.1, C34.1, J7.5, J7.6, J13.3, J14.2, J15.7, R1.1, R5.2, R6.1, R30.2, R31.2, SW1.1, U1.1 (VBAT), U1.13 (VDDA), U1.19 (VDD), U1.32 (VDD), U1.48 (VDDUSB), U1.64 (VDD), U2.3 (VCC), U3.3 (VCC), U6.1 (VOUT), X1.4 (VDD), X2.4 (VCC)
+5V: C42.1, C43.1, J7.3, J7.4, J13.2, J15.8, R2.2, U9.1 (VOUT)
+VBAT: C39.1, C40.1, J4.2, J4.4, J4.6, J4.8, J4.10, R3.2, U8.1 (VOUT)
/*ATTENTION: J5.29, R1.2, U1.20 (PA4)
/*AVI_RST: J5.32, U1.8 (PC0)
/*COMM1_RST: J5.33, U1.10 (PC2)
/*COMM2_RST: J5.34, U1.11 (PC3)
/*EPS_RST: J5.30, U1.21 (PA5)
/*SCI_RST: J5.31, U1.9 (PC1)
/CAN1_H: C10.1, D6.1 (K), J5.40, R7.1, U2.7 (CANH)
/CAN1_L: C12.2, D6.2 (K), J5.38, R8.2, U2.6 (CANL)
/CAN2_H: C14.1, D7.1 (K), J5.39, R9.1, U3.7 (CANH)
/CAN2_L: C16.2, D7.2 (K), J5.37, R10.2, U3.6 (CANL)
/CAN TO USB/ASC1_IN12: J14.4, U1.23 (PA7)
/CAN TO USB/ASC1_IN15: J14.3, U1.26 (PB0)
/CAN TO USB/BOOT: J11.5, R25.1, SW1.2, U1.60 (PH3_BOOT0)
/CAN TO USB/CAN1_RX: U1.61 (PB8), U2.4 (RXD)
/CAN TO USB/CAN1_SHTD: U1.59 (PB7), U2.5 (SHTD)
/CAN TO USB/CAN1_STB: U1.58 (PB6), U2.8 (STB)
/CAN TO USB/CAN1_TX: U1.62 (PB9), U2.1 (TXD)
/CAN TO USB/CAN2_RX: U1.33 (PB12), U3.4 (RXD)
/CAN TO USB/CAN2_SHTD: U1.36 (PB15), U3.5 (SHTD)
/CAN TO USB/CAN2_STB: U1.35 (PB14), U3.8 (STB)
/CAN TO USB/CAN2_TX: U1.34 (PB13), U3.1 (TXD)
/CAN TO USB/EXTI_8: J15.2, U1.41 (PA8)
/CAN TO USB/EXTI_12: J13.6, U1.28 (PB2)
/CAN TO USB/EXTI_13: J7.15, U1.2 (PC13)
/CAN TO USB/EXTI_15: J7.16, U1.4 (PC15)
/CAN TO USB/FTDI1/3V3: C27.1, D10.2 (A), D11.2 (A), U5.3 (VCCIO), U5.10 (3V3OUT), U5.11 (~RESET)
/CAN TO USB/FTDI1/RXLED: R20.2, U5.7 (CBUS2)
/CAN TO USB/FTDI1/TXLED: R19.2, U5.14 (CBUS1)
/CAN TO USB/FTDI1/USB/DN: C29.1, J9.A7 (DN1_A), J9.B7 (DN2_B), R17.1
/CAN TO USB/FTDI1/USB/DP: C28.1, J9.A6 (DP1_A), J9.B6 (DP2_B), R18.1
/CAN TO USB/FTDI/3V3: C21.1, D8.2 (A), D9.2 (A), U4.3 (VCCIO), U4.10 (3V3OUT), U4.11 (~RESET)
/CAN TO USB/FTDI/RXLED: R14.2, U4.7 (CBUS2)
/CAN TO USB/FTDI/TXLED: R13.2, U4.14 (CBUS1)
/CAN TO USB/FTDI/USB/DN: C23.1, J8.A7 (DN1_A), J8.B7 (DN2_B), R11.1
/CAN TO USB/FTDI/USB/DP: C22.1, J8.A6 (DP1_A), J8.B6 (DP2_B), R12.1
/CAN TO USB/HSE_IN: U1.5 (PH0), X1.3 (OUTPUT)
/CAN TO USB/HSE_OE: U1.6 (PH1), X1.1 (TRI-STATE)
/CAN TO USB/I2C2_SCL: J13.5, R31.1, U1.29 (PB10)
/CAN TO USB/I2C2_SDA: J13.4, R30.1, U1.30 (PB11)
/CAN TO USB/LED1: RN1.16 (R), U1.37 (PC6)
/CAN TO USB/LED2: RN1.15 (R), U1.38 (PC7)
/CAN TO USB/LED3: RN1.14 (R), U1.39 (PC8)
/CAN TO USB/LED4: RN1.13 (R), U1.40 (PC9)
/CAN TO USB/LED5: RN1.12 (R), U1.57 (PB5)
/CAN TO USB/NRST: C31.1, J11.4, R6.2, SW2.3, U1.7 (NRST)
/CAN TO USB/OSC_32_IN: U1.3 (PC14), X2.3 (OUT)
/CAN TO USB/SPI3_CS1: J7.14, U1.50 (PA15)
/CAN TO USB/SPI3_CS2: J7.13, U1.54 (PD2)
/CAN TO USB/SPI3_MISO: J7.9, J7.10, U1.52 (PC11)
/CAN TO USB/SPI3_MOSI: J7.11, J7.12, U1.53 (PC12)
/CAN TO USB/SPI3_SCK: J7.7, J7.8, U1.51 (PC10)
/CAN TO USB/SYS_JTMS_SWCLK: J11.3, U1.49 (PA14)
/CAN TO USB/SYS_JTMS_SWDIO: J11.2, U1.46 (PA13)
/CAN TO USB/USART1_CTS: J15.6, U1.56 (PB4)
/CAN TO USB/USART1_RTS: J15.4, U1.55 (PB3)
/CAN TO USB/USART1_RX: J15.3, U1.43 (PA10)
/CAN TO USB/USART1_TX: J15.5, U1.42 (PA9)
/CAN TO USB/USART2_CTS: U1.14 (PA0), U5.2 (~RTS)
/CAN TO USB/USART2_RTS: U1.15 (PA1), U5.6 (~CTS)
/CAN TO USB/USART2_RX: U1.17 (PA3), U5.1 (TXD)
/CAN TO USB/USART2_TX: U1.16 (PA2), U5.4 (RXD)
/CAN TO USB/USART3_CTS: U1.22 (PA6), U4.2 (~RTS)
/CAN TO USB/USART3_RTS: U1.27 (PB1), U4.6 (~CTS)
/CAN TO USB/USART3_RX: U1.25 (PC5), U4.1 (TXD)
/CAN TO USB/USART3_TX: U1.24 (PC4), U4.4 (RXD)
/CAN TO USB/USB_OTG_FS_D+: J10.A6 (DP1_A), J10.B6 (DP2_B), U1.45 (PA12)
/CAN TO USB/USB_OTG_FS_D-: J10.A7 (DN1_A), J10.B7 (DN2_B), U1.44 (PA11)
/CAN TO USB/VBUS1: J2.6, J10.A4_B9 (VBUS), J10.B4_A9 (VBUS__1)
/CAN TO USB/VBUS2: C24.1, FB2.1, J2.4, J9.A4_B9 (VBUS), J9.B4_A9 (VBUS__1)
/CAN TO USB/VBUS3: C18.1, FB1.1, J2.2, J8.A4_B9 (VBUS), J8.B4_A9 (VBUS__1)
/INTERBOARD_CONNECTOR/3V3_1: J1.1, J5.11
/INTERBOARD_CONNECTOR/3V3_2: J1.3, J5.12
/INTERBOARD_CONNECTOR/3V3_3: J1.5, J5.13
/INTERBOARD_CONNECTOR/3V3_4: J1.7, J5.14
/INTERBOARD_CONNECTOR/3V3_5: J1.9, J5.15
/INTERBOARD_CONNECTOR/3V3_6: J1.11, J5.16
/INTERBOARD_CONNECTOR/3V3_7: J1.13, J5.17
/INTERBOARD_CONNECTOR/3V3_8: J1.15, J5.18
/INTERBOARD_CONNECTOR/3V3_9: J1.17, J5.19
/INTERBOARD_CONNECTOR/3V3_10: J1.19, J5.20
/INTERBOARD_CONNECTOR/3V3_11: J1.21, J5.21
/INTERBOARD_CONNECTOR/3V3_12: J1.23, J5.22
/INTERBOARD_CONNECTOR/3V3_13: J1.25, J5.23
/INTERBOARD_CONNECTOR/3V3_14: J1.27, J5.24
/INTERBOARD_CONNECTOR/3V3_15: J1.29, J5.25
/INTERBOARD_CONNECTOR/BATT: J4.1, J5.3, J5.4
/INTERBOARD_CONNECTOR/BATT_1: J4.3, J5.5
/INTERBOARD_CONNECTOR/BATT_2: J4.5, J5.6
/INTERBOARD_CONNECTOR/BATT_3: J4.7, J5.7
/INTERBOARD_CONNECTOR/BATT_4: J4.9, J5.8
/Regulator 3V3/LX1: L3.1, U7.3 (LX1)
/Regulator 3V3/LX2: L3.2, U7.2 (LX2)
/Regulator 3V3/R-: R4.1, R27.1, U7.8 (FB)
/Regulator 3V4/LX1: L4.1, U6.3 (LX1)
/Regulator 3V4/LX2: L4.2, U6.2 (LX2)
/Regulator 3V4/R-: R5.1, R26.1, U6.8 (FB)
/Regulator 4V2/LX1: L2.1, U8.3 (LX1)
/Regulator 4V2/LX2: L2.2, U8.2 (LX2)
/Regulator 4V2/R-: R3.1, R28.1, U8.8 (FB)
/Regulator 5V/LX1: L1.1, U9.3 (LX1)
/Regulator 5V/LX2: L1.2, U9.2 (LX2)
/Regulator 5V/R-: R2.1, R29.1, U9.8 (FB)
GND: C1.2, C2.2, C3.2, C4.2, C5.2, C6.2, C7.2, C8.2, C9.2, C10.2, C11.2, C12.1, C13.2, C14.2, C15.2, C16.1, C17.2, C18.2, C19.2, C20.2, C21.2, C22.2, C23.2, C24.2, C25.2, C26.2, C27.2, C28.2, C29.2, C30.2, C31.2, C32.2, C33.2, C34.2, C35.2, C36.2, C37.2, C38.2, C39.2, C40.2, C41.2, C42.2, C43.2, C44.2, D5.1 (A1), D6.3 (A), D7.3 (A), D12.1 (K), D13.1 (K), D14.1 (K), D15.1 (K), D16.1 (K), H1.1, H2.1, H3.1, H4.1, J3.1, J5.1, J5.2, J5.9, J5.10, J5.26, J5.27, J5.28, J5.35, J5.36, J7.1, J7.2, J8.A1_B12 (GND), J8.B1_A12 (GND__1), J9.A1_B12 (GND), J9.B1_A12 (GND__1), J10.A1_B12 (GND), J10.B1_A12 (GND__1), J11.1, J13.1, J14.1, J15.1, R15.1, R16.1, R21.1, R22.1, R23.1, R24.1, R25.2, R26.2, R27.2, R28.2, R29.2, SW2.4, U1.12 (VSSA), U1.18 (VSS), U1.31 (VSS), U1.47 (VSS), U1.63 (VSS), U2.2 (GND), U2.9 (GND), U3.2 (GND), U3.9 (GND), U4.5 (GND), U4.13 (GND), U5.5 (GND), U5.13 (GND), U6.6 (MODE), U6.7 (GND), U7.6 (MODE), U7.7 (GND), U8.6 (MODE), U8.7 (GND), U9.6 (MODE), U9.7 (GND), X1.2 (GND), X2.2 (GND)
unnamed: C11.1, R7.2, R8.1
unnamed: C15.1, R9.2, R10.1
unnamed: D1.2 (A), J2.5
unnamed: D2.2 (A), J2.3
unnamed: D3.2 (A), J2.1
unnamed: D4.2 (A), D5.2 (A2), J3.2
unnamed: D8.1 (K), R13.1
unnamed: D9.1 (K), R14.1
unnamed: D10.1 (K), R19.1
unnamed: D11.1 (K), R20.1
unnamed: D12.2 (A), RN1.1 (R)
unnamed: D13.2 (A), RN1.2 (R)
unnamed: D14.2 (A), RN1.3 (R)
unnamed: D15.2 (A), RN1.4 (R)
unnamed: D16.2 (A), RN1.5 (R)
unnamed: J8.A5 (CC1_A), R15.2
unnamed: J8.B5 (CC2_B), R16.2
unnamed: J9.A5 (CC1_A), R21.2
unnamed: J9.B5 (CC2_B), R22.2
unnamed: J10.A5 (CC1_A), R23.2
unnamed: J10.B5 (CC2_B), R24.2
unnamed: R11.2, U4.9 (USBDM)
unnamed: R12.2, U4.8 (USBDP)
unnamed: C19.1, C20.1, FB1.2, U4.12 (VCC)
unnamed: R17.2, U5.9 (USBDM)
unnamed: R18.2, U5.8 (USBDP)
unnamed: C25.1, C26.1, FB2.2, U5.12 (VCC)
VBUS: C35.1, C38.1, C41.1, C44.1, D1.1 (K), D2.1 (K), D3.1 (K), D4.1 (K), U6.4 (VIN), U6.5 (EN), U7.4 (VIN), U7.5 (EN), U8.4 (VIN), U8.5 (EN), U9.4 (VIN), U9.5 (EN)
